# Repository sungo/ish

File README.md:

# ish

The ish, yet another Corne-ish keyboard

# What

The ish is a Corne-ish split 42-key keyboard, specifically designed for the [nice!nano](https://nicekeyboards.com/nice-nano), bluetooth/battery operation, and [ZMK](https://zmk.dev).

The ish has the following features/anti-features:

- Support for _both_ Choc v1 and Cherry MX switches, which can be used at the
  same time
- Keys are Cherry MX spaced (I have fat fingers)
- Designed for battery and bluetooth, via the nice!nano controller
- Does _not_ have LEDs, underglow or otherwise, nor OLED displays
- Relatively easy to build
- Based on the Corne v3

As of v2.0, the ish is known to work with a regular non-LED non-display Corne
profile using KMK and ZMK, including as a wired split. It has been tested with
nice!nano v2 and Adafruit Kee-boar controller.

## Controller Warning

If you want to use something other than a nice!nano, do _not_ connect the
battery. I'm not aware of another pro micro compat controller, other than the
nice!nano, with battery circuitry. You will most likely fry any other controller
and probably damage the battery and maybe cause a fire. 

# Why

Well, gotta learn kicad somehow and the Corne is one of my favorite boards. Like all keyboard people though, I have capital-T Thoughts about the Corne so why not learn kicad by tweaking the Corne.

Also to be clear, this is built with me, sungo, in mind. I will be super thrilled if other folks like it but this board is to make me happy and serve as a learning experience.

## Just give me the gerbers, dammit

The gerbers for the v1.0 are available [here](gerbers/ish-1.0.0-gerbers.zip). Top and bottom plates [are available](gerbers/) as well though regular Corne plates work just fine if you have those already.

Gerbers for v2.0 are coming soon

# Goals

* a choc build based on the Corne v3 platform. The v3 simplified the board a great deal, particularly by making it not reversible.
* Wireless first. Built specifically for the nice!nano, the ish comes with battery wiring and a power switch
* Fuck LEDs. I don't use LEDs or OLEDs on my battery builds so they're gone
* All going well, don't change anything that would break compatibility with the Corne v3 plates

# Design Principles

AKA arbitrary rules I made up for myself

* Fuck branding. If you've ever read Pattern Recognition by William Gibson, I have a branding allergy similar to Cayce Pollard. I _hate_ that most keyboards come slathered in URLs, cute logos, names, etc. 
* Limit the amount of traces on the top surface
* Put as few traces on the top surface under the MCU as possible (It's way too easy to crap up a board by cutting traces while trying to get a stuck hotswap MCU off the board)
* Limit soldering to one side
* Keep solder points and electronics away from the edges
* On an individual board, diodes all go the same direction

# Questions

## Why are the switches reversed on one half?

This is the result of a few of the design principles. The Corne v2 and the Corne v3 end up putting diodes and solder pads on the edge of the board on one half because there's no where else for them to go. On the other side, one direction conflicts with the standoff annular ring placement.  So, if I want to keep the diodes and pads away from the board edge and I don't want to move the annular rings, one half of the board must have switches that go the other direction. If I toss my rule against breaking v3 plate compatibility, I'll revisit this.

# BOM

## Required parts that the board was designed around

These parts were specifically used in the design process. If you find other working options, please let me know.

- [Two nice!nano controllers](https://nicekeyboards.com/nice-nano/) soldered with machine pins
- [Two PCM12SMTR slide switches](https://www.digikey.com/en/products/detail/c-k/PCM12SMTR/1640112?s=N4IgTCBcDaIAQDYCMSC0AFAwgWSWAytgCoBKcIAugL5A)
- [Two EVQ-P7A01P momentary switches](https://www.digikey.com/en/products/detail/panasonic-electronic-components/EVQ-P7A01P/4429447)
- [Two S02B-XASS-1 JST connectors](https://www.digikey.com/en/products/detail/jst-sales-america-inc/S02B-XASS-1/1634785)
- [Two lithpoly batteries _with protection circuits_](https://www.digikey.com/en/products/detail/adafruit-industries-llc/1570/5054546) - the protection circuits are really important as the ish has no onboard battery management of its own

## Other bits and bobs

- [42 diodes](https://www.digikey.com/en/products/detail/comchip-technology/CDSW4148-G/3308608)
- [Machine pin headers](https://www.amazon.com/gp/product/B0187LTEX2/) that, once installed, are at least 4mm tall to fit the battery
- 42 Choc v1 hotswap sockets, switches and caps and/or 42 Cherry/MX hostswap sockets, switches and caps

# License

The original Corne is licensed under the MIT license so the ish is as well.

- - -

Copyright © 2022-2023 sungo

Corne v3, kbd library © 2019-2022 foostan

Permission is hereby granted, free of charge, to any person obtaining a copy of this software and associated documentation files (the “Software”), to deal in the Software without restriction, including without limitation the rights to use, copy, modify, merge, publish, distribute, sublicense, and/or sell copies of the Software, and to permit persons to whom the Software is furnished to do so, subject to the following conditions:

The above copyright notice and this permission notice shall be included in all copies or substantial portions of the Software.

THE SOFTWARE IS PROVIDED “AS IS”, WITHOUT WARRANTY OF ANY KIND, EXPRESS OR IMPLIED, INCLUDING BUT NOT LIMITED TO THE WARRANTIES OF MERCHANTABILITY, FITNESS FOR A PARTICULAR PURPOSE AND NONINFRINGEMENT. IN NO EVENT SHALL THE AUTHORS OR COPYRIGHT HOLDERS BE LIABLE FOR ANY CLAIM, DAMAGES OR OTHER LIABILITY, WHETHER IN AN ACTION OF CONTRACT, TORT OR OTHERWISE, ARISING FROM, OUT OF OR IN CONNECTION WITH THE SOFTWARE OR THE USE OR OTHER DEALINGS IN THE SOFTWARE.

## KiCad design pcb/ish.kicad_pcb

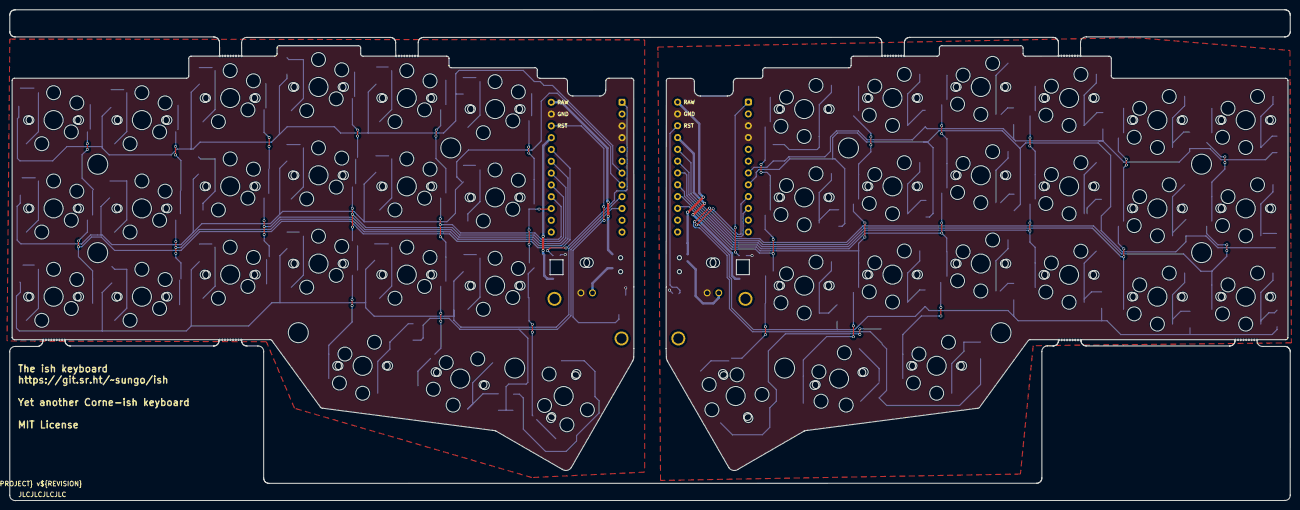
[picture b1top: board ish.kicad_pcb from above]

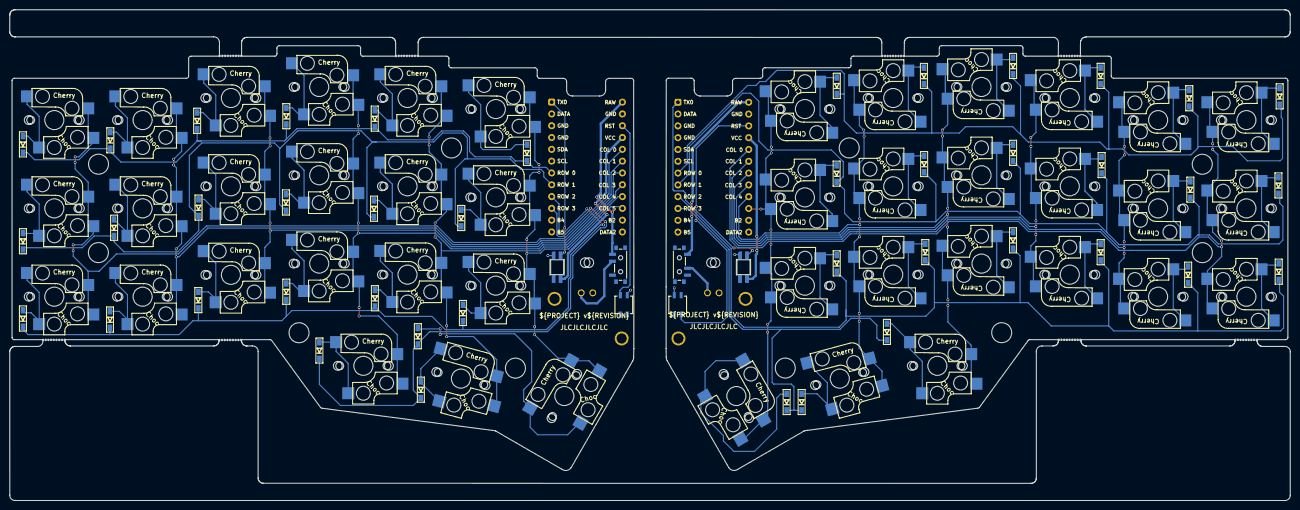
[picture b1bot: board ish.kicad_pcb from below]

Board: 2 copper layers, 275.5 x 105.6 mm, 98 parts (42 on the bottom side), 64 nets.

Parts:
D1, D2, D3, D4, D5, D6, D7, D8, D9, D10, D11, D12, D13, D14, D15, D16, D17, D18, D19, D20, D21, D22, D23, D24, D25, D26, D27, D28, D29, D30, D31, D32, D33, D34, D35, D36, D37, D38, D39, D40, D41, D42: D; D3_SMD_v2
Ref**: Val**; Standoff Hole
Ref**#2, Ref**#3, Ref**#4, Ref**#5, Ref**#6, Ref**#7, Ref**#8: Val**; Standoff Hole
Ref**#9, Ref**#10, Ref**#11, Ref**#12: Val**; M2_HOLE_v2
SW1, SW2, SW3, SW4, SW5, SW6, SW7, SW8, SW9, SW10, SW11, SW12, SW13, SW14, SW15, SW16, SW17, SW18, SW19, SW20, SW21, SW22, SW23, SW24, SW25, SW26, SW27, SW28, SW29, SW30, SW31, SW32, SW33, SW34, SW35, SW36, SW37, SW38, SW39, SW40, SW41, SW42: SW_PUSH; CherryMX_MidHeight_Choc_Hotswap
U1, U2: ProMicro; ProMicro_v3 Chips Down

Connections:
GND: U1.3, U1.4, U1.23
GNDA: U2.3, U2.4, U2.23
unnamed: D1.2, SW1.2
unnamed: D2.2, SW2.2
unnamed: D3.2, SW3.2
unnamed: D4.2, SW4.2
unnamed: D5.2, SW5.2
unnamed: D6.2, SW6.2
unnamed: D7.2, SW7.2
unnamed: D8.2, SW8.2
unnamed: D9.2, SW9.2
unnamed: D10.2, SW10.2
unnamed: D11.2, SW11.2
unnamed: D12.2, SW12.2
unnamed: D13.2, SW13.2
unnamed: D14.2, SW14.2
unnamed: D15.2, SW15.2
unnamed: D16.2, SW16.2
unnamed: D17.2, SW17.2
unnamed: D18.2, SW18.2
unnamed: D19.2, SW19.2
unnamed: D20.2, SW20.2
unnamed: D21.2, SW21.2
unnamed: D22.2, SW22.2
unnamed: D23.2, SW23.2
unnamed: D24.2, SW24.2
unnamed: D25.2, SW25.2
unnamed: D26.2, SW26.2
unnamed: D27.2, SW27.2
unnamed: D28.2, SW28.2
unnamed: D29.2, SW29.2
unnamed: D30.2, SW30.2
unnamed: D31.2, SW31.2
unnamed: D32.2, SW32.2
unnamed: D33.2, SW33.2
unnamed: D34.2, SW34.2
unnamed: D35.2, SW35.2
unnamed: D36.2, SW36.2
unnamed: D37.2, SW37.2
unnamed: D38.2, SW38.2
unnamed: D39.2, SW39.2
unnamed: D40.2, SW40.2
unnamed: D41.2, SW41.2
unnamed: D42.2, SW42.2
col0: SW1.1, SW7.1, SW13.1, U1.20
col0_r: SW22.1, SW28.1, SW34.1, U2.20
col1: SW2.1, SW8.1, SW14.1, U1.19
col1_r: SW23.1, SW29.1, SW35.1, U2.19
col2: SW3.1, SW9.1, SW15.1, U1.18
col2_r: SW24.1, SW30.1, SW36.1, U2.18
col3: SW4.1, SW10.1, SW16.1, SW19.1, U1.17
col3_r: SW25.1, SW31.1, SW37.1, SW40.1, U2.17
col4: SW5.1, SW11.1, SW17.1, SW20.1, U1.16
col4_r: SW26.1, SW32.1, SW38.1, SW41.1, U2.16
col5: SW6.1, SW12.1, SW18.1, SW21.1, U1.15
col5_r: SW27.1, SW33.1, SW39.1, SW42.1, U2.15
row0: D1.1, D2.1, D3.1, D4.1, D5.1, D6.1, U1.7
row0_r: D22.1, D23.1, D24.1, D25.1, D26.1, D27.1, U2.7
row1: D7.1, D8.1, D9.1, D10.1, D11.1, D12.1, U1.8
row1_r: D28.1, D29.1, D30.1, D31.1, D32.1, D33.1, U2.8
row2: D13.1, D14.1, D15.1, D16.1, D17.1, D18.1, U1.9
row2_r: D34.1, D35.1, D36.1, D37.1, D38.1, D39.1, U2.9
row3: D19.1, D20.1, D21.1, U1.10
row3_r: D40.1, D41.1, D42.1, U2.10

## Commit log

2022-06-28 init
2022-06-28 gerbers for 0.0.1
2022-06-28 update footprint 3d models
2022-06-28 license
2022-06-28 readme with images
2022-07-11 docs and images for the v0.0.1 build
2022-07-19 bring in switch and bottom plates
2022-07-19 fancy rounded version
2022-07-19 hopefully rev 0.1.0 with new battery hookup and minor placement tweaks elsewhere
2022-08-06 config sync
2022-08-06 v0.1.0 gerbers
2023-01-23 revision is now 1.0.0
2023-01-23 gerbers for ish v1.0.0
2023-01-23 gerbers for top and bottom plate
2023-03-07 update to kicad7 and tweak the battery pads a bit
2023-03-07 version string update
2023-03-07 update plates to kicad7
2023-03-07 remove rounded version
2023-03-09 undo the trace spacing changes I made to work with the rounding/melting plugin
2023-03-09 new v1.0.0 gerbers
2023-03-17 update docs and images for the final ish v1 design
2023-03-19 move the lib into the root of the repo so everyone can use it
2023-03-19 switch the ish v1 to use the new library path
2023-07-23 readme update for v1.1.0
2023-07-23 ish v1.1.0 with lots of new features:
    - battery hookup via JST instead of solder points
    - regular corne compatible TRRS for wired split
    - now supports both MX and Choc v1 switches which can be used at the
    same time
    - support for an electronics cover has been _removed_ to cram in all the
    new bits
2023-11-24 ish v2.0.0
    - now supports both MX and Choc v1 switches which can be used at the same time
    - MCU is chips-down again to match the industry
    - new smaller power and reset switches that fit under the pcb without
    adding thickness
    - battery is connected via a reenforced JST
    - support for an electronics cover has been _removed_
2023-11-25 add a signal led
2023-11-27 put the cover screw holes back
    required moving things around a little and doing some routing that I'm
    not super thrilled with. (The signal led's fault, tbh.) I _think_ I got
    the screw holes in the right place.
